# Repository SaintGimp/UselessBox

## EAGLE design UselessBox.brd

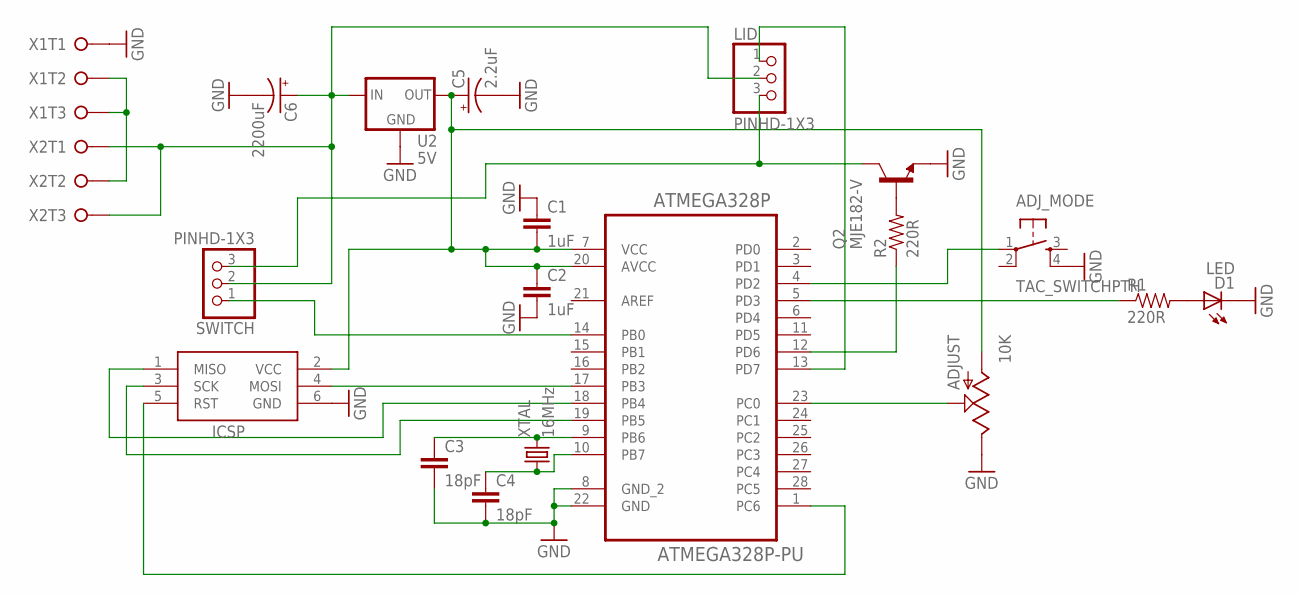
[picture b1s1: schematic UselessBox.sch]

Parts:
ADJUST: 10K; POT-3362U
ADJ_MODE: TAC_SWITCHPTH; TACTILE-SWITCH-6MM
ATMEGA328P: ATMEGA328P-PU; DIP28
C1, C2: 1uF; CAPACITOR-5MM
C3, C4: 18pF; CAPACITOR-2.5MM
C5: 2.2uF; CAP-POL-2.5-5
C6: 2200uF; CAP-POL-5-10
D1: LED; LED5MM
ICSP: AVRISP-6; AVRISP
LID: PINHD-1X3; 1X03
Q2: MJE182-V; TO225AA-V
R1, R2: 220R; AXIAL-7.5MM
SWITCH: PINHD-1X3; 1X03
U2: 5V; TO92-INLINE
X1, X2: SCREW-TERM-3
XTAL: 16MHz; CRYSTAL-V

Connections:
GND: ADJUST.P$1 (E), ADJ_MODE.4, ATMEGA328P.8 (GND_2), ATMEGA328P.22 (GND), C1.1, C2.2, C3.2, C4.2, C5.-, C6.-, D1.K (C), ICSP.6 (GND), Q2.E, U2.2 (GND), X1.1
unnamed: ATMEGA328P.13 (PD7), LID.1
unnamed: ADJ_MODE.1, ATMEGA328P.4 (PD2)
unnamed: ATMEGA328P.19 (PB5), ICSP.3 (SCK)
unnamed: ATMEGA328P.18 (PB4), ICSP.1 (MISO)
unnamed: ATMEGA328P.17 (PB3), ICSP.4 (MOSI)
unnamed: ATMEGA328P.1 (PC6), ICSP.5 (RST)
unnamed: ATMEGA328P.14 (PB0), SWITCH.1
unnamed: ATMEGA328P.9 (PB6), C3.1, XTAL.2
unnamed: ATMEGA328P.10 (PB7), C4.1, XTAL.1
unnamed: ATMEGA328P.12 (PD6), R2.P$1 (1)
unnamed: LID.3, Q2.C, SWITCH.3
unnamed: X1.2, X1.3, X2.2
unnamed: ADJUST.P$2 (S), ATMEGA328P.23 (PC0)
unnamed: Q2.B, R2.P$2 (2)
unnamed: D1.A, R1.P$2 (2)
unnamed: ATMEGA328P.5 (PD3), R1.P$1 (1)
VCC: ADJUST.P$3 (A), ATMEGA328P.7 (VCC), ATMEGA328P.20 (AVCC), C1.2, C2.1, C5.+, ICSP.2 (VCC), U2.1 (OUT)
VIN: C6.+, LID.2, SWITCH.2, U2.3 (IN), X2.1, X2.3

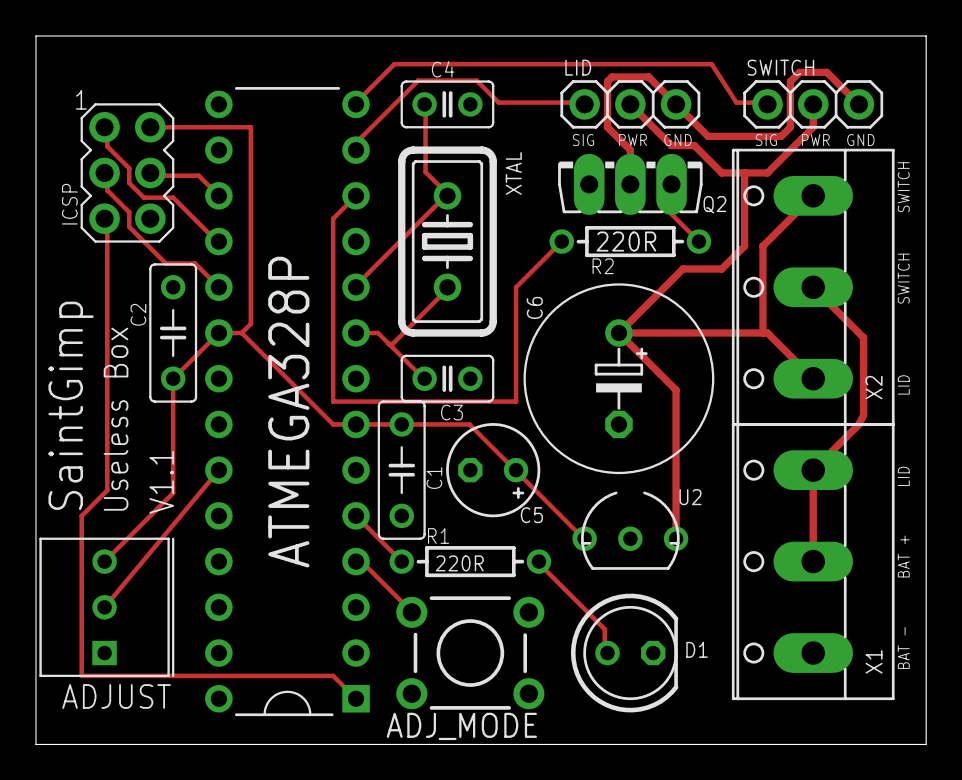
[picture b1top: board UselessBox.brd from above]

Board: 2 copper layers, 49.5 x 39.4 mm, 20 parts (0 on the bottom side), 19 nets.

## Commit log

2015-03-11 Initial commit of files
2015-03-17 Increase strength of arm/shaft interface
2015-03-17 Controller board
2015-03-18 Better power traces and polish tweaks
2015-03-20 Update size of bypass caps
2015-03-20 Update parts from library
2015-04-29 New inside pieces and major code refactor
2015-04-29 Tweak patterns and add a couple new ones
2015-05-02 Add better RNG
2016-12-22 Adjust timings
2017-03-03 Update laser cutting file for the box
2018-08-27 Improve timings
